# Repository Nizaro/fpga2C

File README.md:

# fpga2C

Design of a system that grab the data from an image sensor to an fpga

# Repo structure

/Materiel.ods - initial research on which board to use (as well as cameras.)
/Pinout.ods - signal assignation in the design (HDL signal name, ZTurn pin name, and header pin number), as well as trace lengths and differential skew in the PCB.

/JLCPCB_Multilayer - an example Kicad project containing the appropriate constraints for a JLCPCB order.
/Kick - the main KiCad project, containing the schematic, the PCB and its output products, and custom component libraries.
/PCB-Output-Products - contains the output products (Gerbers and drill files) of the two main PCBs

/ZTurnV2 - the main Vivado project. 
/archive - old versions of IPs handy to keep around. 
/constraints - constraint files for the ZTurnV2 board, to be used if elaboration I/O planning fails. 
/drivers - preliminary folder containing software drivers for custom IPs. 
/interface_repo - contains the custom-made LVDS interface specification. 
/ip_repo - contains the custom IPs. 
/infos_vivado - miscellaneous files for Vivado installation and debugging. 
/petalinux - the PetaLinux build and working directory. 
/sd_backup - a backup of the factory boot image found in the SD card of the ZTurnV2, and its Linux device tree for reference. 
/vitis_workspace - the main Vitis workpace, containing the hardware platform and the application for software development. 

/doc - main documentation folder. 
/doc/PCB_LVDS - useful guidelines for designing PCBs with LVDS or HF capabilities. 
/doc/Vivado_AXI - product guides for used IPs and AXI interface specs. 
/doc/ZTurnV2 - schematics and manuals for the ZTurnV2 and associated devices. 
/doc/Zynq7 - info for developing for the Zynq7. 
/doc/capteur_lentille - info about the sensor and the lens.

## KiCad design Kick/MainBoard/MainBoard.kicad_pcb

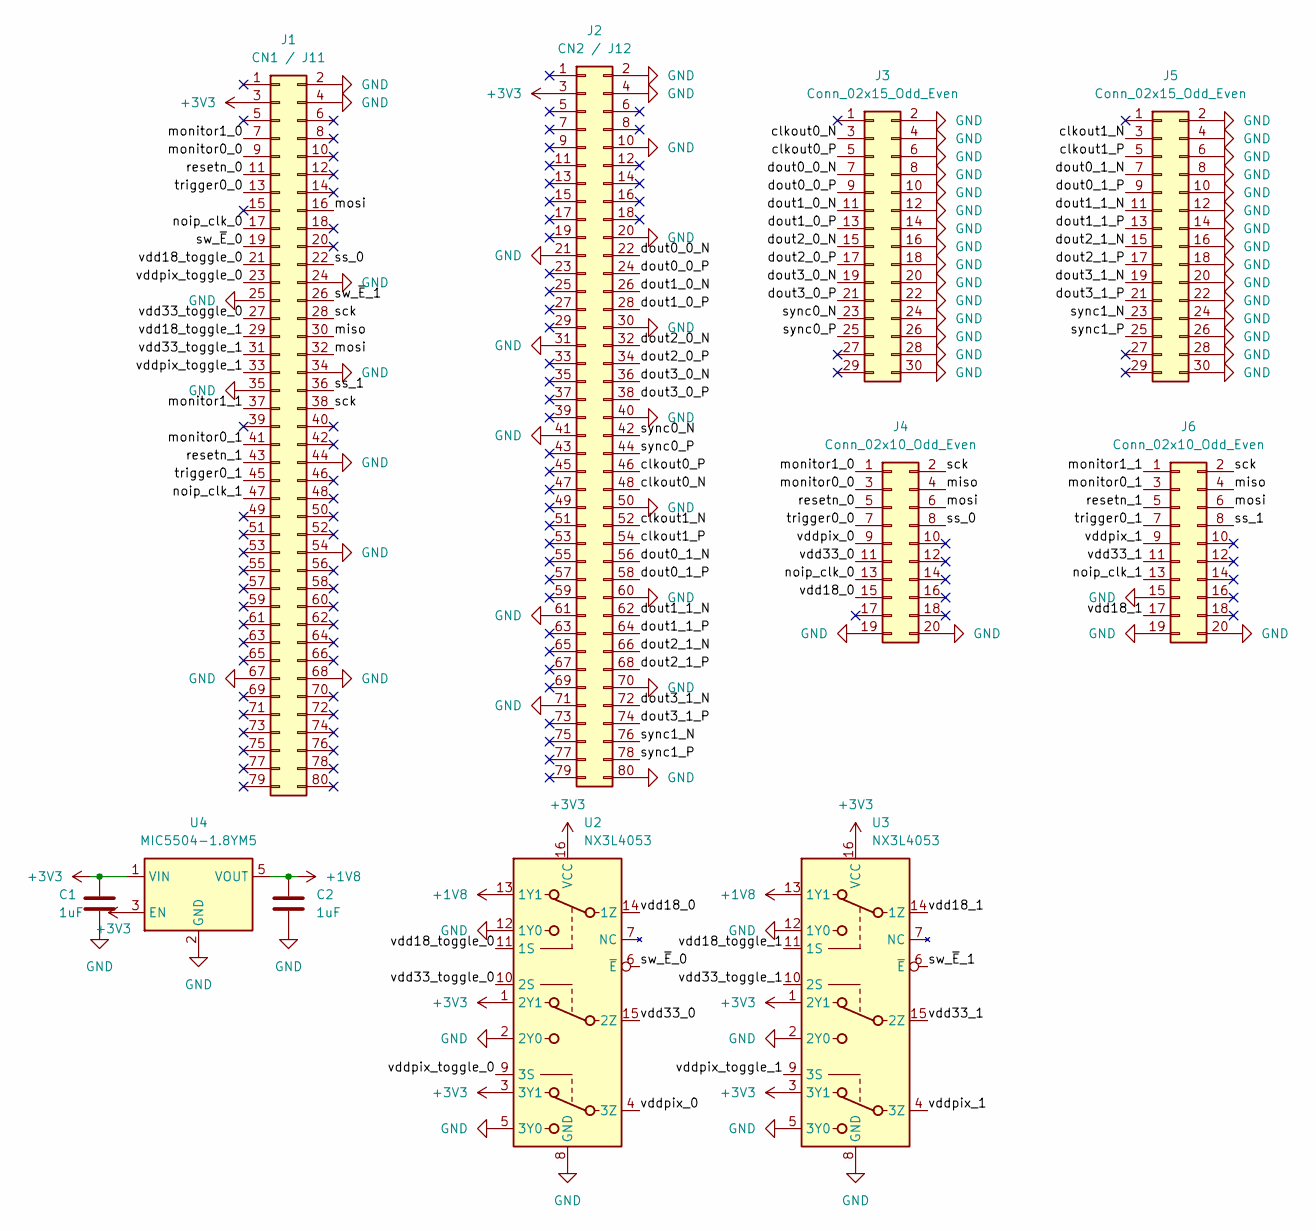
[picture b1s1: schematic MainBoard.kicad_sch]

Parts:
C1, C2: 1uF; C_0603_1608Metric
J1: CN1 / J11; SAMTEC_TFM-140-12-L-D-A; LCSC Part TFM-140-12-L-D-A
J2: CN2 / J12; SAMTEC_TFM-140-12-L-D-A; LCSC Part TFML-140-12-L-D-A
J3, J5: Conn_02x15_Odd_Even; SAMTEC_TFML-115-02-L-D-LC
J4, J6: Conn_02x10_Odd_Even; SAMTEC_TFML-110-02-L-D-LC-TR
U2, U3: NX3L4053; SOP65P640X110-16N
U4: MIC5504-1.8YM5; SOT-23-5

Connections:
+1V8: C2.1, U2.13 (1Y1), U3.13 (1Y1), U4.5 (VOUT)
+3V3: C1.1, J1.3, J2.3, U2.1 (2Y1), U2.3 (3Y1), U2.16 (VCC), U3.1 (2Y1), U3.3 (3Y1), U3.16 (VCC), U4.1 (VIN), U4.3 (EN)
/clkout0_N: J2.48, J3.3
/clkout0_P: J2.46, J3.5
/clkout1_N: J2.52, J5.3
/clkout1_P: J2.54, J5.5
/dout0_0_N: J2.22, J3.7
/dout0_0_P: J2.24, J3.9
/dout0_1_N: J2.56, J5.7
/dout0_1_P: J2.58, J5.9
/dout1_0_N: J2.26, J3.11
/dout1_0_P: J2.28, J3.13
/dout1_1_N: J2.62, J5.11
/dout1_1_P: J2.64, J5.13
/dout2_0_N: J2.32, J3.15
/dout2_0_P: J2.34, J3.17
/dout2_1_N: J2.66, J5.15
/dout2_1_P: J2.68, J5.17
/dout3_0_N: J2.36, J3.19
/dout3_0_P: J2.38, J3.21
/dout3_1_N: J2.72, J5.19
/dout3_1_P: J2.74, J5.21
/miso: J1.30, J4.4, J6.4
/monitor0_0: J1.9, J4.3
/monitor0_1: J1.41, J6.3
/monitor1_0: J1.7, J4.1
/monitor1_1: J1.37, J6.1
/mosi: J1.16, J1.32, J4.6, J6.6
/noip_clk_0: J1.17, J4.13
/noip_clk_1: J1.47, J6.13
/resetn_0: J1.11, J4.5
/resetn_1: J1.43, J6.5
/sck: J1.28, J1.38, J4.2, J6.2
/ss_0: J1.22, J4.8
/ss_1: J1.36, J6.8
/sw_~E_0: J1.19, U2.6 (~E)
/sw_~E_1: J1.26, U3.6 (~E)
/sync0_N: J2.42, J3.23
/sync0_P: J2.44, J3.25
/sync1_N: J2.76, J5.23
/sync1_P: J2.78, J5.25
/trigger0_0: J1.13, J4.7
/trigger0_1: J1.45, J6.7
/vdd18_0: J4.15, U2.14 (1Z)
/vdd18_1: J6.17, U3.14 (1Z)
/vdd33_0: J4.11, U2.15 (2Z)
/vdd33_1: J6.11, U3.15 (2Z)
/vdd33_toggle_0: J1.27, U2.10 (2S)
/vdd33_toggle_1: J1.31, U3.10 (2S)
/vddpix_0: J4.9, U2.4 (3Z)
/vddpix_1: J6.9, U3.4 (3Z)
/vddpix_toggle_0: J1.23, U2.9 (3S)
/vddpix_toggle_1: J1.33, U3.9 (3S)

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
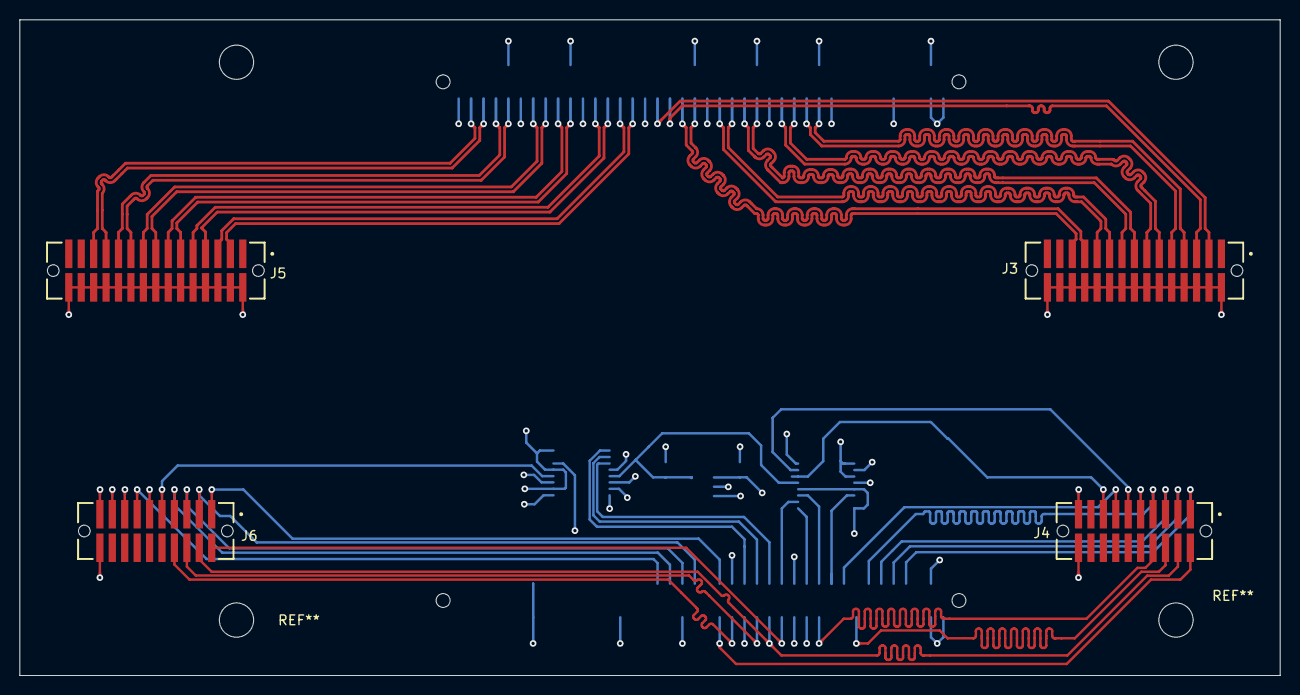
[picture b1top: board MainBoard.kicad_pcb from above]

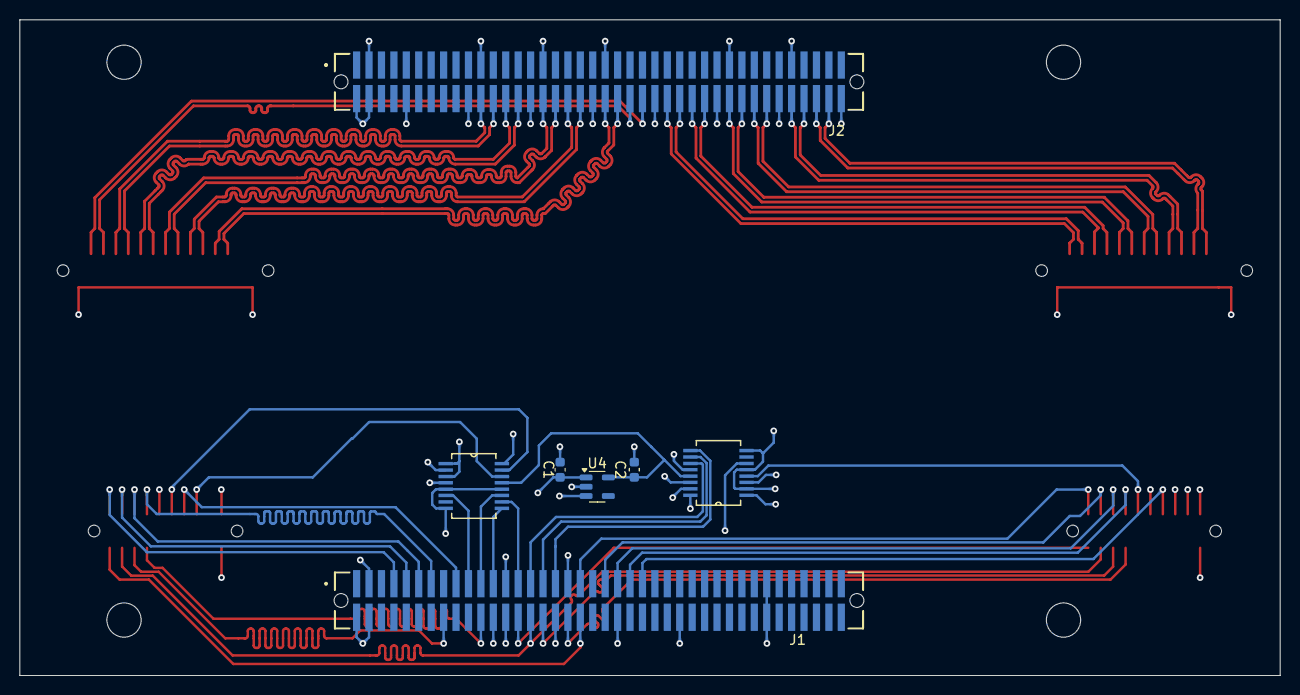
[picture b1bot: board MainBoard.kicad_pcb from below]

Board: 4 copper layers, 128.8 x 67.0 mm, 11 parts (7 on the bottom side), 56 nets.

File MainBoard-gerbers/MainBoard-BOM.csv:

Comment,Designator,Footprint,LCSC Part Number,Quantity
OddEven,"J6,J4",SAMTEC_TFML-110-02-L-D-LC-TR,TFML-110-02-L-D-LC,2
OddEven,"J3,J5",SAMTEC_TFML-115-02-L-D-LC,TFML-115-02-L-D-LC,2
OddEven,J1,SAMTEC_TFM-140-12-L-D-A,TFM-140-12-L-D-A,1
1uF,"C2,C1",C_0603_1608Metric,CL10B105KA8NNWC,2
OddEven,J2,SAMTEC_TFM-140-12-L-D-A,TFM-140-12-L-D-A,1

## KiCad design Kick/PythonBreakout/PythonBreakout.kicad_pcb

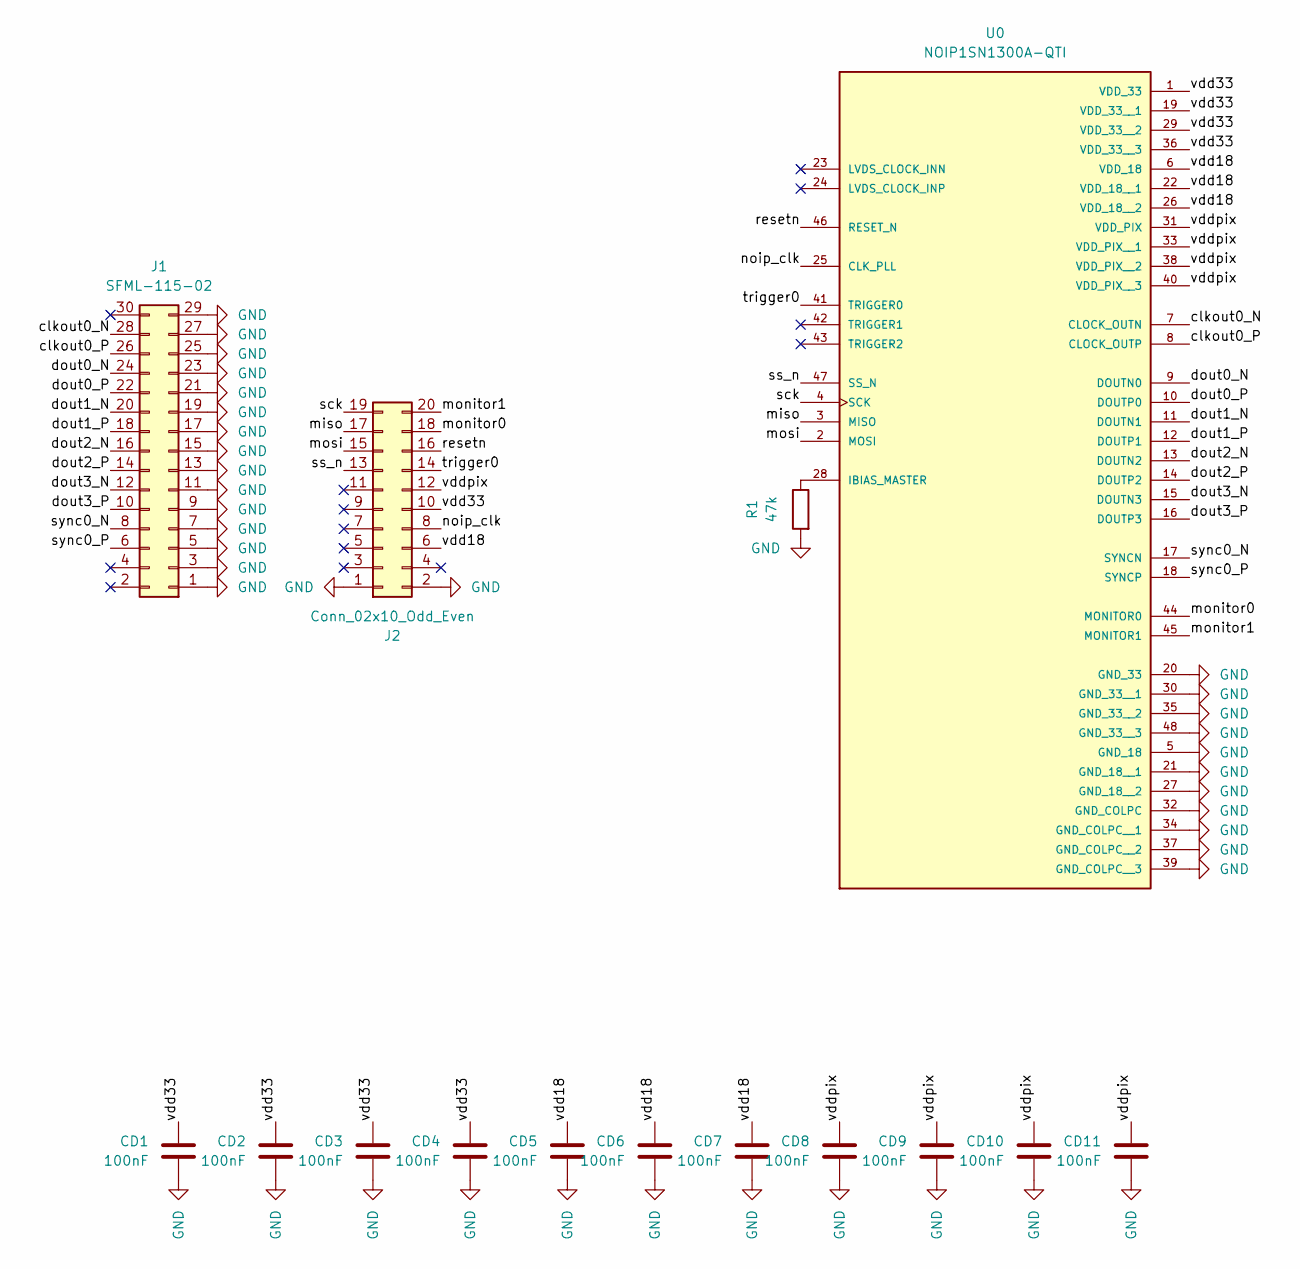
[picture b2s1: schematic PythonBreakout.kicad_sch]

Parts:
CD1, CD2, CD3, CD4, CD5, CD6, CD7, CD8, CD9, CD10, CD11: 100nF; C_0603_1608Metric
J1: SFML-115-02; SAMTEC_SFML-115-02-L-D-LC
J2: Conn_02x10_Odd_Even; SAMTEC_SFML-110-02-L-D-LC
R1: 47k; R_0603_1608Metric
U0: NOIP1SN1300A-QTI; LCC101P1422X1422X228-48N; PARTREV 6

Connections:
/clkout0_N: J1.28, U0.7 (CLOCK_OUTN)
/clkout0_P: J1.26, U0.8 (CLOCK_OUTP)
/dout0_N: J1.24, U0.9 (DOUTN0)
/dout0_P: J1.22, U0.10 (DOUTP0)
/dout1_N: J1.20, U0.11 (DOUTN1)
/dout1_P: J1.18, U0.12 (DOUTP1)
/dout2_N: J1.16, U0.13 (DOUTN2)
/dout2_P: J1.14, U0.14 (DOUTP2)
/dout3_N: J1.12, U0.15 (DOUTN3)
/dout3_P: J1.10, U0.16 (DOUTP3)
/miso: J2.17, U0.3 (MISO)
/monitor0: J2.18, U0.44 (MONITOR0)
/monitor1: J2.20, U0.45 (MONITOR1)
/mosi: J2.15, U0.2 (MOSI)
/noip_clk: J2.8, U0.25 (CLK_PLL)
/resetn: J2.16, U0.46 (RESET_N)
/sck: J2.19, U0.4 (SCK)
/ss_n: J2.13, U0.47 (SS_N)
/sync0_N: J1.8, U0.17 (SYNCN)
/sync0_P: J1.6, U0.18 (SYNCP)
/trigger0: J2.14, U0.41 (TRIGGER0)
/vdd18: CD5.1, CD6.1, CD7.1, J2.6, U0.6 (VDD_18), U0.22 (VDD_18__1), U0.26 (VDD_18__2)
/vdd33: CD1.1, CD2.1, CD3.1, CD4.1, J2.10, U0.1 (VDD_33), U0.19 (VDD_33__1), U0.29 (VDD_33__2), U0.36 (VDD_33__3)
/vddpix: CD8.1, CD9.1, CD10.1, CD11.1, J2.12, U0.31 (VDD_PIX), U0.33 (VDD_PIX__1), U0.38 (VDD_PIX__2), U0.40 (VDD_PIX__3)
GND: CD1.2, CD2.2, CD3.2, CD4.2, CD5.2, CD6.2, CD7.2, CD8.2, CD9.2, CD10.2, CD11.2, J1.1, J1.3, J1.5, J1.7, J1.9, J1.11, J1.13, J1.15, J1.17, J1.19, J1.21, J1.23, J1.25, J1.27, J1.29, J2.1, J2.2, R1.2, U0.5 (GND_18), U0.20 (GND_33), U0.21 (GND_18__1), U0.27 (GND_18__2), U0.30 (GND_33__1), U0.32 (GND_COLPC), U0.34 (GND_COLPC__1), U0.35 (GND_33__2), U0.37 (GND_COLPC__2), U0.39 (GND_COLPC__3), U0.48 (GND_33__3)
unnamed: R1.1, U0.28 (IBIAS_MASTER)

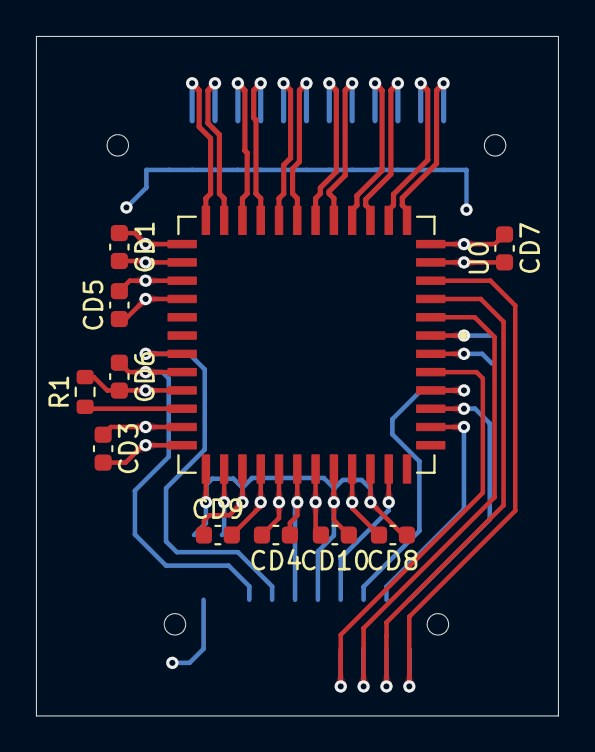
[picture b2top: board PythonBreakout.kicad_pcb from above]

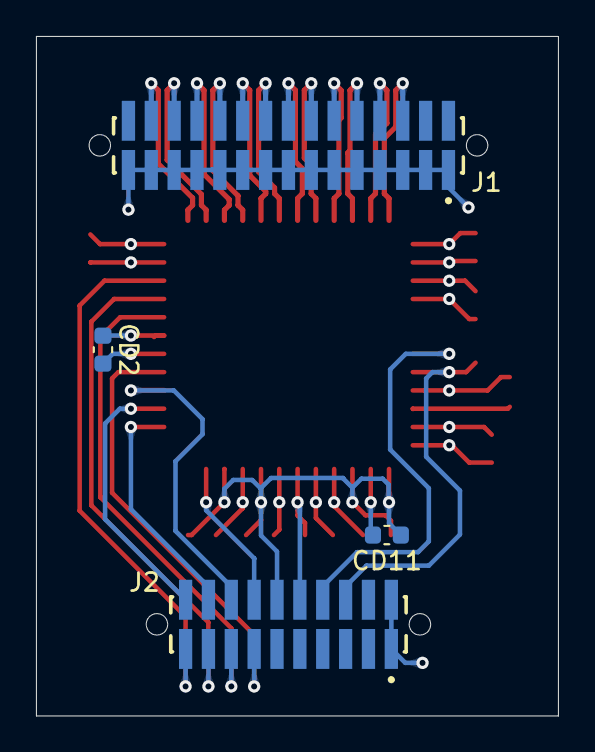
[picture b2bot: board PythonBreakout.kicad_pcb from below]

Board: 4 copper layers, 29.0 x 37.8 mm, 15 parts (4 on the bottom side), 26 nets.

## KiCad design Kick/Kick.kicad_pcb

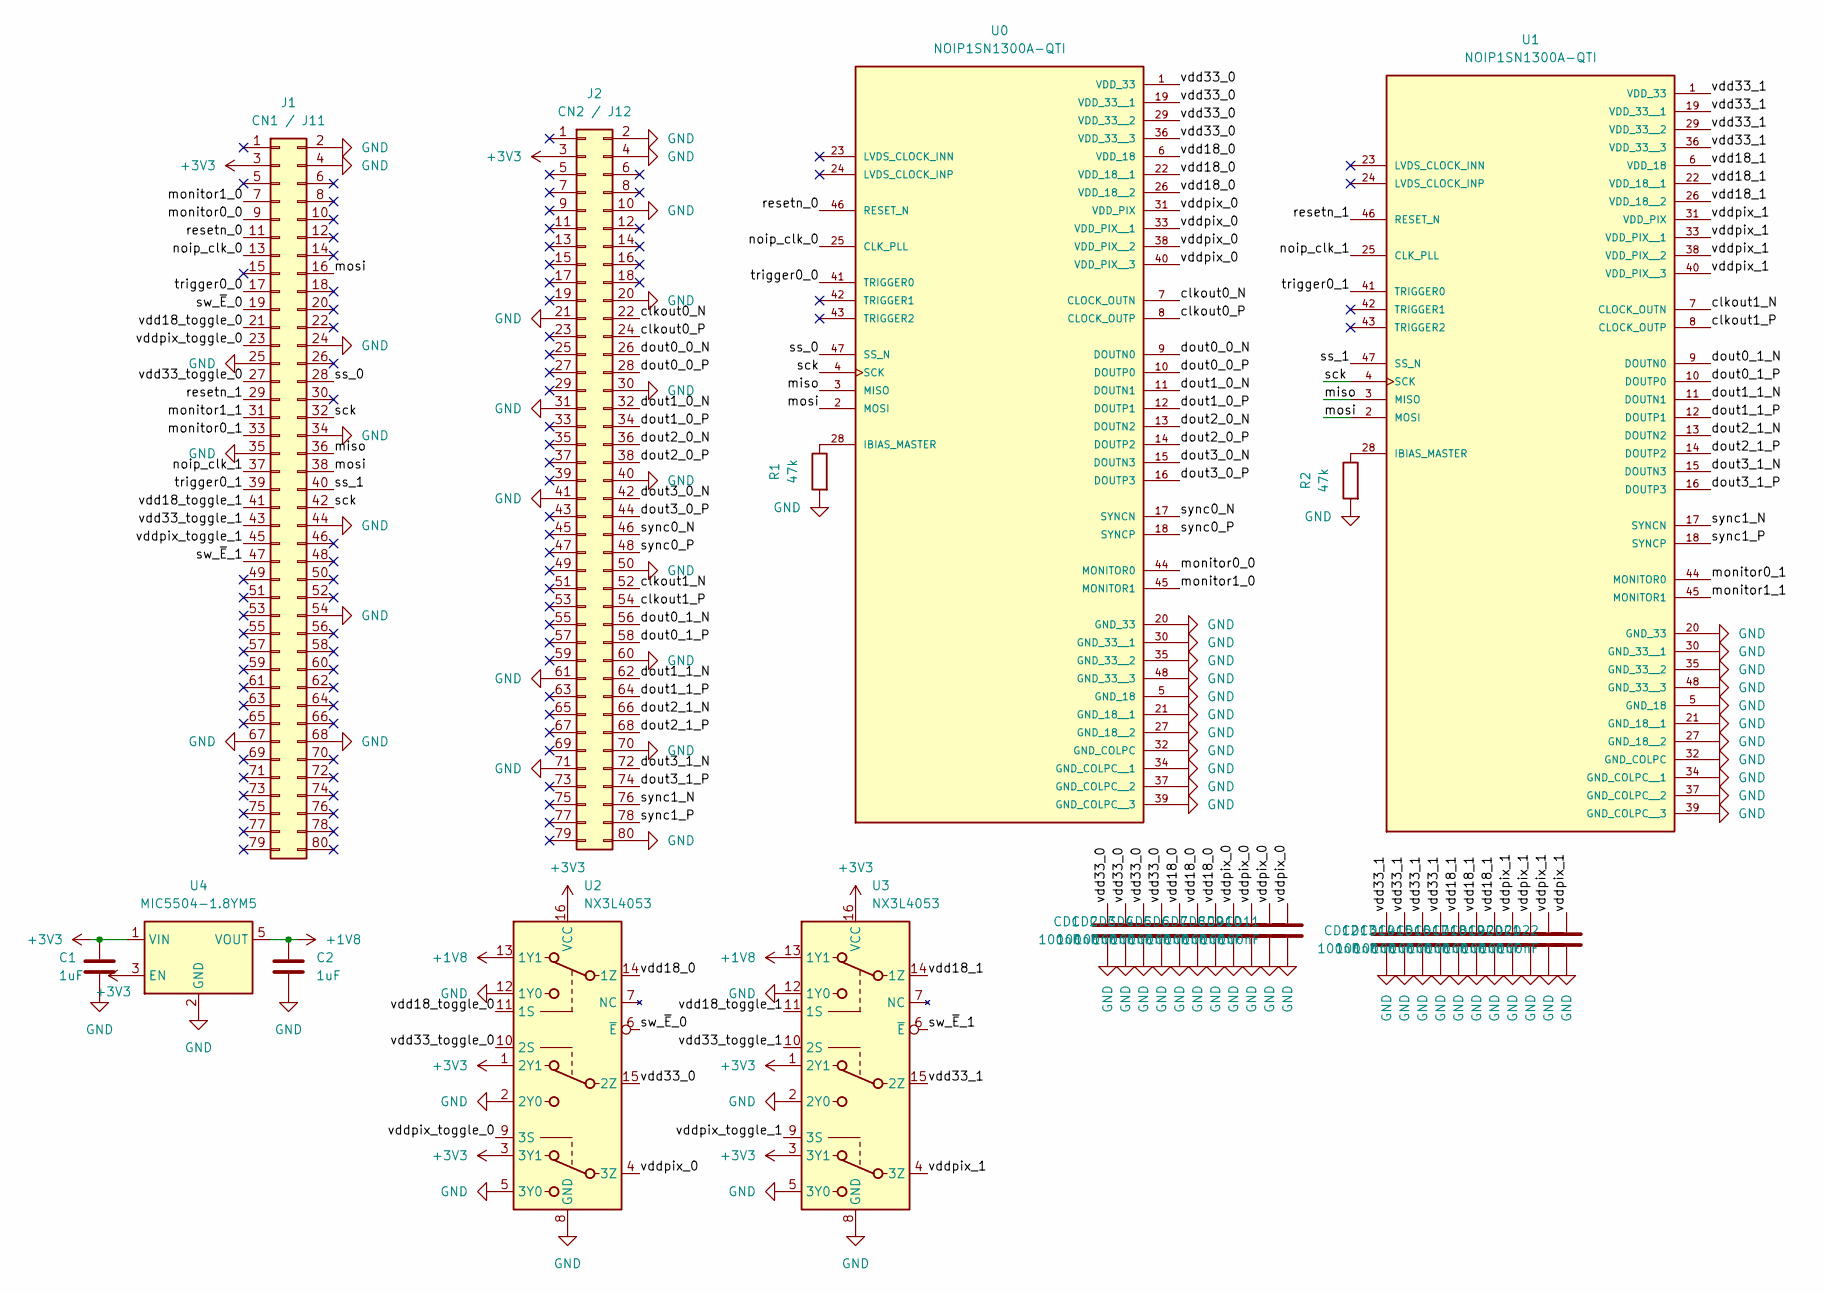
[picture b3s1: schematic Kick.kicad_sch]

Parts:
C1, C2: 1uF; C_0603_1608Metric
CD1, CD2, CD3, CD4, CD5, CD6, CD7, CD8, CD9, CD10, CD11, CD12, CD13, CD14, CD15, CD16, CD17, CD18, CD19, CD20, CD21, CD22: 100nF; C_0603_1608Metric
J1: CN1 / J11; SAMTEC_TFM-140-12-L-D-A
J2: CN2 / J12; SAMTEC_TFM-140-12-L-D-A
R1, R2: 47k; R_0603_1608Metric
U0, U1: NOIP1SN1300A-QTI; LCC101P1422X1422X228-48N; PARTREV 6
U2, U3: NX3L4053; SOP65P640X110-16N
U4: MIC5504-1.8YM5; SOT-23-5

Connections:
+1V8: C2.1, U2.13 (1Y1), U3.13 (1Y1), U4.5 (VOUT)
+3V3: C1.1, J1.3, J2.3, U2.1 (2Y1), U2.3 (3Y1), U2.16 (VCC), U3.1 (2Y1), U3.3 (3Y1), U3.16 (VCC), U4.1 (VIN), U4.3 (EN)
/clkout0_N: J2.22, U0.7 (CLOCK_OUTN)
/clkout0_P: J2.24, U0.8 (CLOCK_OUTP)
/clkout1_N: J2.52, U1.7 (CLOCK_OUTN)
/clkout1_P: J2.54, U1.8 (CLOCK_OUTP)
/dout0_0_N: J2.26, U0.9 (DOUTN0)
/dout0_0_P: J2.28, U0.10 (DOUTP0)
/dout0_1_N: J2.56, U1.9 (DOUTN0)
/dout0_1_P: J2.58, U1.10 (DOUTP0)
/dout1_0_N: J2.32, U0.11 (DOUTN1)
/dout1_0_P: J2.34, U0.12 (DOUTP1)
/dout1_1_N: J2.62, U1.11 (DOUTN1)
/dout1_1_P: J2.64, U1.12 (DOUTP1)
/dout2_0_N: J2.36, U0.13 (DOUTN2)
/dout2_0_P: J2.38, U0.14 (DOUTP2)
/dout2_1_N: J2.66, U1.13 (DOUTN2)
/dout2_1_P: J2.68, U1.14 (DOUTP2)
/dout3_0_N: J2.42, U0.15 (DOUTN3)
/dout3_0_P: J2.44, U0.16 (DOUTP3)
/dout3_1_N: J2.72, U1.15 (DOUTN3)
/dout3_1_P: J2.74, U1.16 (DOUTP3)
/miso: J1.36, U0.3 (MISO), U1.3 (MISO)
/monitor0_0: J1.9, U0.44 (MONITOR0)
/monitor0_1: J1.33, U1.44 (MONITOR0)
/monitor1_0: J1.7, U0.45 (MONITOR1)
/monitor1_1: J1.31, U1.45 (MONITOR1)
/mosi: J1.16, J1.38, U0.2 (MOSI), U1.2 (MOSI)
/noip_clk_0: J1.13, U0.25 (CLK_PLL)
/noip_clk_1: J1.37, U1.25 (CLK_PLL)
/resetn_0: J1.11, U0.46 (RESET_N)
/resetn_1: J1.29, U1.46 (RESET_N)
/sck: J1.32, J1.42, U0.4 (SCK), U1.4 (SCK)
/ss_0: J1.28, U0.47 (SS_N)
/ss_1: J1.40, U1.47 (SS_N)
/sw_~E_0: J1.19, U2.6 (~E)
/sw_~E_1: J1.47, U3.6 (~E)
/sync0_N: J2.46, U0.17 (SYNCN)
/sync0_P: J2.48, U0.18 (SYNCP)
/sync1_N: J2.76, U1.17 (SYNCN)
/sync1_P: J2.78, U1.18 (SYNCP)
/trigger0_0: J1.17, U0.41 (TRIGGER0)
/trigger0_1: J1.39, U1.41 (TRIGGER0)
/vdd18_0: CD5.1, CD6.1, CD7.1, U0.6 (VDD_18), U0.22 (VDD_18__1), U0.26 (VDD_18__2), U2.14 (1Z)
/vdd18_1: CD16.1, CD17.1, CD18.1, U1.6 (VDD_18), U1.22 (VDD_18__1), U1.26 (VDD_18__2), U3.14 (1Z)
/vdd33_0: CD1.1, CD2.1, CD3.1, CD4.1, U0.1 (VDD_33), U0.19 (VDD_33__1), U0.29 (VDD_33__2), U0.36 (VDD_33__3), U2.15 (2Z)
/vdd33_1: CD12.1, CD13.1, CD14.1, CD15.1, U1.1 (VDD_33), U1.19 (VDD_33__1), U1.29 (VDD_33__2), U1.36 (VDD_33__3), U3.15 (2Z)
/vdd33_toggle_0: J1.27, U2.10 (2S)
/vdd33_toggle_1: J1.43, U3.10 (2S)
/vddpix_0: CD8.1, CD9.1, CD10.1, CD11.1, U0.31 (VDD_PIX), U0.33 (VDD_PIX__1), U0.38 (VDD_PIX__2), U0.40 (VDD_PIX__3), U2.4 (3Z)
/vddpix_1: CD19.1, CD20.1, CD21.1, CD22.1, U1.31 (VDD_PIX), U1.33 (VDD_PIX__1), U1.38 (VDD_PIX__2), U1.40 (VDD_PIX__3), U3.4 (3Z)
/vddpix_toggle_0: J1.23, U2.9 (3S)
/vddpix_toggle_1: J1.45, U3.9 (3S)
unnamed: R1.1, U0.28 (IBIAS_MASTER)
unnamed: R2.1, U1.28 (IBIAS_MASTER)

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
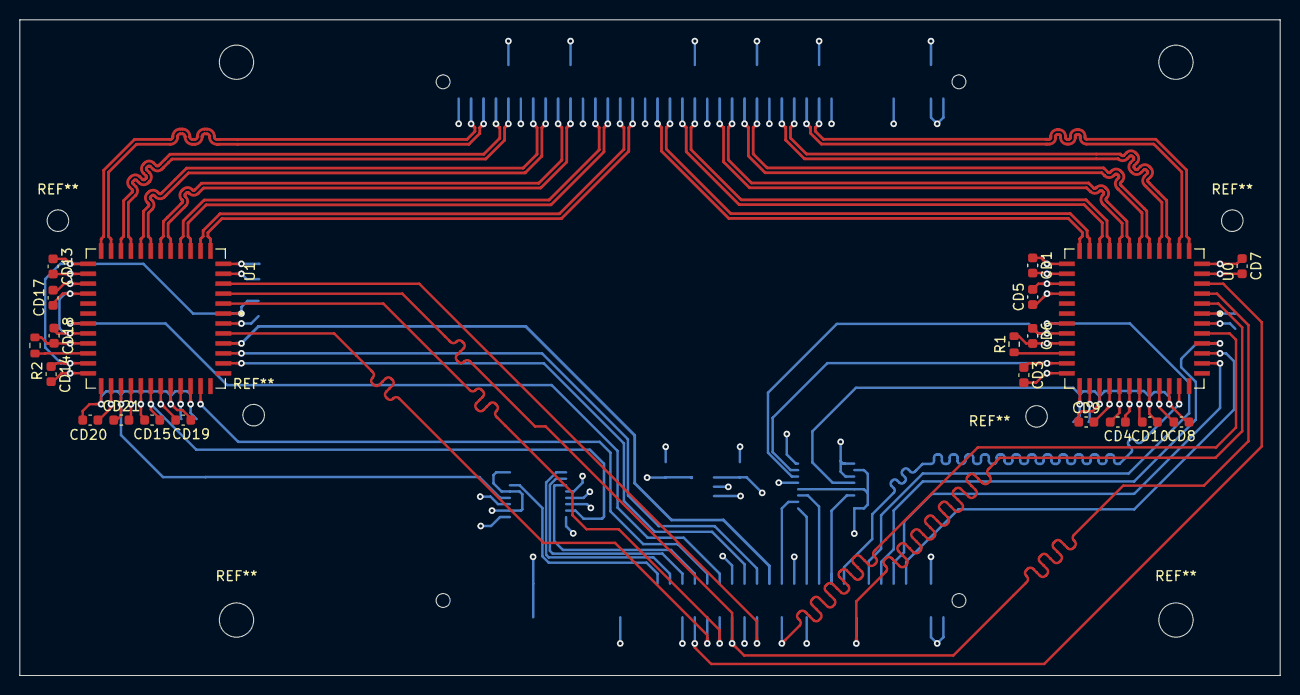
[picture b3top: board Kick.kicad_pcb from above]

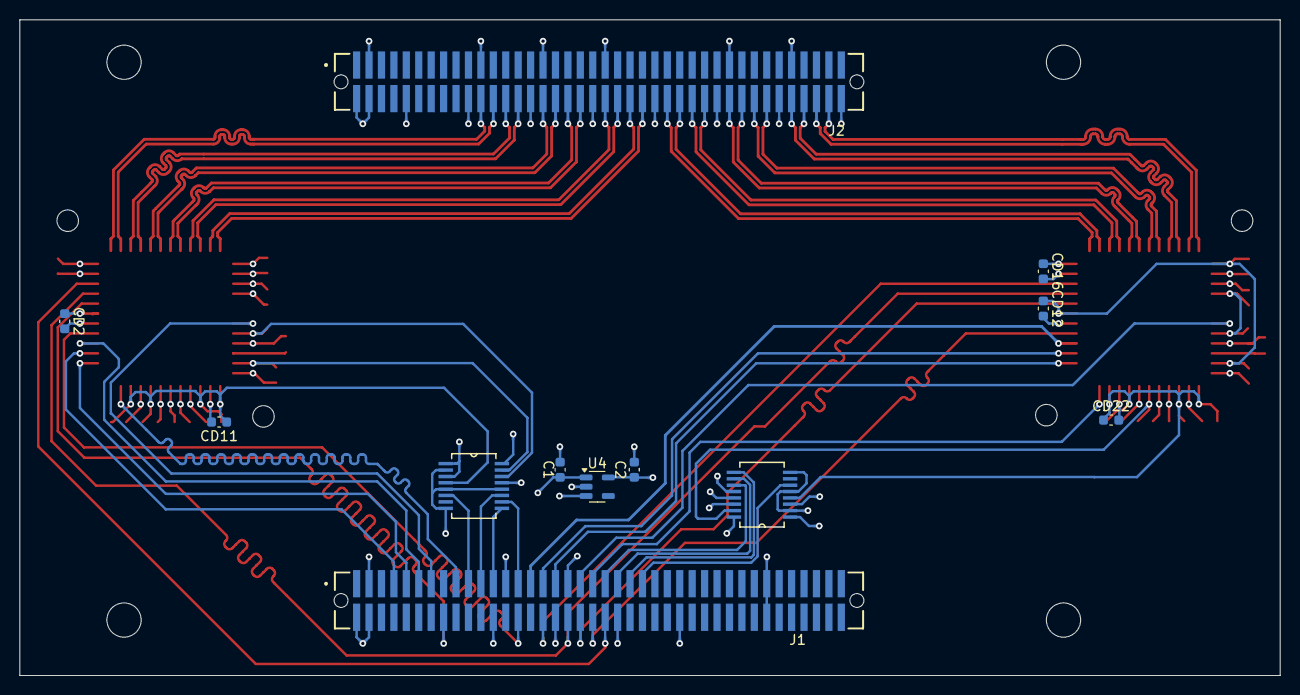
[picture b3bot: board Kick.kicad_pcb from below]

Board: 4 copper layers, 128.8 x 67.0 mm, 33 parts (12 on the bottom side), 58 nets.

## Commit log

2024-06-20 initial commit : upload of vivado projects, notes, and docs
2024-06-20 fixed syntax issue in noip_ctrl's flagprocess
2024-06-20 integrated noip_ctrl and noip_lvds_driver_stream to BD
2024-06-20 implemented all external ports save for lvds.
2024-06-20 completed block design with all modules, validated
2024-06-20 first attempt to fix memory bug
2024-06-21 pinned out whole system, implemented. temporary fix for image memory bug
2024-06-21 tested and fix'd noip control. currently fixing inter-clock slack
2024-06-21 fixed timing issues (wrong clock port for spi_clk_in). spi interface awaiting testing.
2024-06-21 proper clocking of all spi signal, no more edge issues for spi clock
2024-06-24 in-entity clk testing (72M_pll, spi_cl)
2024-06-24 spi interface tested. outlining startup config with onsemi website.<
2024-06-25 moved vitis platform to repo, imported and verified hardware
2024-06-25 created first (very early) boot image
2024-06-25 started PCB routing with new voltage regulators
2024-06-26 acurrate placement of devices, HF impedance calculation
2024-06-26 calculated new, thinner track widths for 7628 stackup.
2024-06-26 routed lvds pairs, mean skew 0.37mm
2024-06-27 re-calculated and re-traced wider lvds traces for correct dielectric thickness
2024-06-27 optimized placement of via next to the 2 NOIP2
2024-06-27 routed U1's side and power supply.
2024-06-27 preliminary routing (lacking spi and monitors), prior to setting correct distance between sensors
2024-06-28 repositioned sensors and rerouted diff pairs
2024-06-28 finished routing and drc
2024-06-28 reduced length of bottom traces
2024-07-01 added mounting holes for lens holder and rerouted long bottom traces from J11
2024-07-01 decoupled noip power pins
2024-07-02 validated skew of single-ended signals with new clock delays
2024-07-02 length-matched spi signals
2024-07-02 reasonable intra-pair skew on NOIP1
2024-07-02 replicated all length changes to NOIP0. no differential skew.
2024-07-02 started verbose PCB documentation
2024-07-03 added BOM and external sources to PCB doc
2024-07-03 issue #2 : added mounting holes to connect to the Zturn's screw holes
2024-07-03 issue #1 : added repo organization to README
2024-07-04 issue #4 : decoupled ALL power pairs of sensors and added decoupling caps to schematic for easy reference
2024-07-04 separated the two board and started routing python_breakout with several connectors
2024-07-05 tried several connectors, chose TFML/SFML. routing LVDS witb 0 skew.
2024-07-05 routed PythonBreakout with SFML
2024-07-08 routed 0 side on MainBoard with TFMLs
2024-07-08 routed bottom part with length matching
2024-07-08 routed all layers, length matched top part and updated models
2024-07-08 updated pinout and checked length timing
2024-07-09 verificated and generated output products for both boards
2024-07-09 added inverters to LVDS pairs in Vivado and updated pin placement
2024-07-10 started software doc
2024-07-10 started advanced axi simulation project
2024-07-11 built new test platform and fleshed out doc
2024-07-11 attempted to fix xil_types inclusion problem for custom noip_ctrl drivers (in sdt)
2024-07-12 wrote spi startup commands for sensor (custom ctrl driver 0)
2024-07-12 moved to new platform, removed inclusion of NOIP drivers. moving back to rtl simulation
2024-07-12 added AXI VIP to ctrl testing
2024-07-15 new IP doc and transaction tb for noip_ctrl (register 0)
2024-07-15 fixed valid/ready handshake on noip_ctrl startup commands
2024-07-15 new export products with BOMs and position files for PCBA
2024-07-15 updated output files to match JLC specs
2024-07-15 actual working commit
2024-07-16 fixed spi read (reg 1) on noip_ctrl
2024-07-16 tested all operations of noip_ctrl
2024-07-16 implemented automatic alignment on lvds channels
2024-07-17 added incomplete word support to lvds_stream auto-alignment
2024-07-17 fixed slack and clock paths on hardware side : remaining methodology violations are asynchronous i/o delays
2024-07-17 redesigned fsm for lvds_stream and tested full frame readout (without memory)
2024-07-18 implemented line RAM on streamer
2024-07-18 first try at HDMI imp (with Xilinx Mixer and AXIS to Video)
2024-07-18 new IP for HDMI (hdmi_ctrl), without using the Xil IPs
2024-07-18 pinned out and validated HDMI interface
2024-07-19 changed hdmi interface to faster clock for main process
2024-07-22 added hdmi IP, UART, and embedded Ethernet interface - fixed implementation error on tri-state pins
2024-07-22 remade a new software platform to try to fix library issues with new drivers
2024-07-23 removed standalone support for vitis platform, moving towards dma-oriented data transfers (without xaxidma)
2024-07-23 fixed realignment in streamer for negative bitslips
2024-07-24 first implementation of line-by-line MM2S readout
2024-07-24 implemented write fifo for streamer and 8-bit support - trying to fix vivado crash
2024-07-24 fixed critical vivado glitch - attempting to implement 32-bit read fifo
2024-07-25 fixed constant generation for 8-bit/10-bit mode
2024-07-25 implemented read and write fifo on streamer, moving towards dma implementation
2024-07-26 managed to get past implementation with new streamer - fixing methodology problems.
2024-07-26 prior to MMCM-based solution to clock paths
2024-07-29 fixed word_ready process but there are still timing issues remaining
2024-07-29 removed unnecessary LUT in streamer, slightly improving setup timing violations
2024-07-30 fixed lvds_clk1 setup by using MMCM / created RGB led controller
2024-07-30 reduced freq of LVDS clocks, increased freq of PS7, attempting reset replication
2024-07-31 fixed most clock violations, only setup (data) violations remaining. also fixed gccio (so changed pin placement)
2024-07-31 commit prior to using SERDES to fix streamer timing violations
2024-08-01 design changes; implemented first streamer with SelectIO, no more timing violations. Confirming complete design.
2024-08-05 implemented selectio for both sensors, attempting to fix unconnected design issue
2024-08-06 selectio and unconnected net issues fixed : no more lvds clock issues. aiming for better placement to reduce inter-clock paths setup violations.
2024-08-06 fixed noip_ctrl and changed several reset allocations to comply with timing
2024-08-07 new design and PCB with available clock pins and LED pins. Still cross-domain timing issues.
2024-08-09 changed hardware platform and fleshed out doc, updated PCB output products
2024-08-13 completed Quickstart
2024-09-29 misc. commit before local deletion
